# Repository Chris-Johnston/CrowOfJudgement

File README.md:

# Crow of Judgement

An LED Christmas ornament based on the "Crow of Judgement" meme.

# What?

# What, actually?

This is a meme which was common among my friends from school (aka "robocrob"). As a 
last-minute secret santa idea, I designed this circuitboard and made a few for gifts.

The circuit is really basic. It's just a switch, resistor, and two very bright red LEDs powered by a CR2032 coin cell battery.

I used KiCad to design the board. I traced the crow of judgement image
using Inkscape and the [svg2mod](https://github.com/svg2mod/svg2mod) tool to
convert my vector trace into the footprint.

I included pins on the board so that you can easily connect external power sources, if you want PWM or just don't want to use a battery.
The footprints for the parts are placed on the back, but the LEDs are meant
to go on the opposite side. This was done so that the silkscreen on the front
side was kept clean.

Because of the last minute nature of when I decided to start the project and
the amount of time it takes to have PCBs made (including in a pandemic),
I rushed the design of these by keeping them as simple as possible.
Maybe next year I could incorporate a microcontroller and make this more hackable. Only a few 4 AM nights were required to wrap this up.

# Build Guide

These are some basic instructions intended for those with some prior soldering experience
and some understanding of surface mount soldering, intended for those that I gifted
these ornaments to.

Also yes, I realize that many of these images are somewhat out of focus and
that my work surface was a bit dusty. No I don't plan on retaking these images.

## Parts

You should have:
  - The circuitboard
  - 2 LEDs (red)
  - 2 surface-mount resistors (40 ohm 1206 package, one extra)
  - 1 surface-mount switch
  - 1 coin-cell battery holder for a CR2032
  - 1 CR2032 battery
  - 1 piece of string to hang the ornament with

This page will provide some non-specific details for how to assemble the item.

## Tools Required

You'll need:
  - A soldering iron with a relatively fine tip
  - Solder
  - A room with good air circulation

Nice to have:
  - Diagonal cutters
  - Tweezers or pliers
  - Solder wick

# Assembly

## 1. Surface Mount Parts

The surface mount parts are the hardest part, luckily there aren't that many of them. It's good to get them out of the way first.
The challenge with these parts is that you have to keep them steady in the right place.

In general the technique I use is:
1. Tin one pad of the package very slightly.
2. Line up the package, ideally with tweezers or pliers.
3. With one hand heat the tinned pad and with the other hold the package in place.
4. Once the package is secure, solder the remaining pads. (In this case there are only 2.)

That's what I do here with the switch. I would actually recommend instead starting with the resistors, since I gave you 2, but the switch is
a bigger package so it will be easier.

Tin one pad for the component.

Place the part in place, hold it steady with the tweezers, heat up the pre-tinned side, then solder the other side.
The switch is not directional, so it can go either way. Neither are the resistors.

The switch should stand up a little bit. Unfortunately the part I picked kinda sucks. It sticks out from the board, and the switch is flush in the casing.
You will need a screwdriver or a pencil to flip the switch back and forth.

Next, I soldered the resistor. They are not directional, so don't worry if the numbers don't add up.
I provided 2 because they are very tiny and easy to lose.

If it turns out that the pads have too much solder, that's why solder wick is handy.

Congrats! That's the hard part!

## 2. Through-Hole Parts

Next up are the through-hole parts. If you know how to solder, you know how to solder these. If you don't for some reason, there are many guides or you can just DM me.

Both of these parts are directional. If you mess up everything completely in reverse, it will probably still work, but if any less then it won't work.

Start with the battery holder.

The square side of the battery holder goes on the **+** end, facing outwards on the **back** of the board. Place the board down on the battery holder and solder the two pins.

The battery holder pins are very sharp, and are in an area where you might place your hand! Be sure to trim the pins off when you are done so they aren't so sharp!

_This goes without saying, but you are also probably soldering with lead. Please don't lick the board, because lead isn't good for you._

All that's left are the LEDs.

You will probably know this already, but it's good to double check. LEDs have a flat edge on one side, one leg which is shorter, and you can also check what the inside of the LED looks like. **Match up the short leg (-) with the square hole (also labelled - on the back)!**

When soldering the LEDs, you may want to bend the pins a bit so that the LED stays in place. Even when pulled tight, it will have a small amount of wiggle room for adjustment. Be sure to trim these pins as well.

_Note:_ If the switch turns out to be really bad, you could probably use one leg of the LEDs to jump the two pins for the switch in its place. This will leave things permanently on.

## 3. Insert Battery + Hang with String

That's it! All that's left is to insert the battery. It should go in only one way, with the positive end of the battery facing outwards.

The holes in the top of the board can be used to thread twine through, with knots in the back to hold it in place.

# Some Things You Should Know

- The holes in the top are meant to run thread through to hang it up as an ornament. This is not pictured in the photos seen here, because I didn't have the thread yet.

- The power switch kinda sucks because I didn't get the right part. You'll want to use something to flip the switch.

- The LEDs are super bright, I have not done the math for how long it will stay on. I doubt it will be very long. Turn it off when you are done, or prepare some extra CR2032 batteries.

- The 3v3 and GND pins in the corner are meant to be an external power source. Want to hook this up to an Arduino? Go ahead!

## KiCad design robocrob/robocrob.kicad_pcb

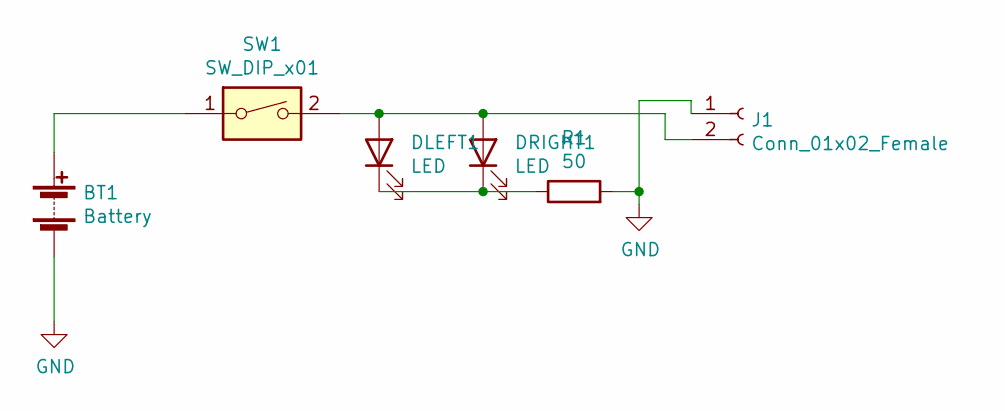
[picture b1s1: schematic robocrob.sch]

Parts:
BT1: Battery; BatteryHolder_ComfortableElectronic_CH273-2450_1x2450
DLEFT1: LED; LED_D5.0mm
DRIGHT1: LED; LED_D5.0mm
J1: Conn_01x02_Female; PinSocket_1x02_P2.54mm_Vertical
R1: 50; R_1206_3216Metric_Pad1.42x1.75mm_HandSolder
SW1: SW_DIP_x01; SW_DIP_SPSTx01_Slide_6.7x4.1mm_W8.61mm_P2.54mm_LowProfile

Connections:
GND: BT1.2 (-), J1.1, R1.2
unnamed: BT1.1 (+), SW1.1
unnamed: DLEFT1.1 (K), DRIGHT1.1 (K), R1.1
unnamed: DLEFT1.2 (A), DRIGHT1.2 (A), J1.2, SW1.2

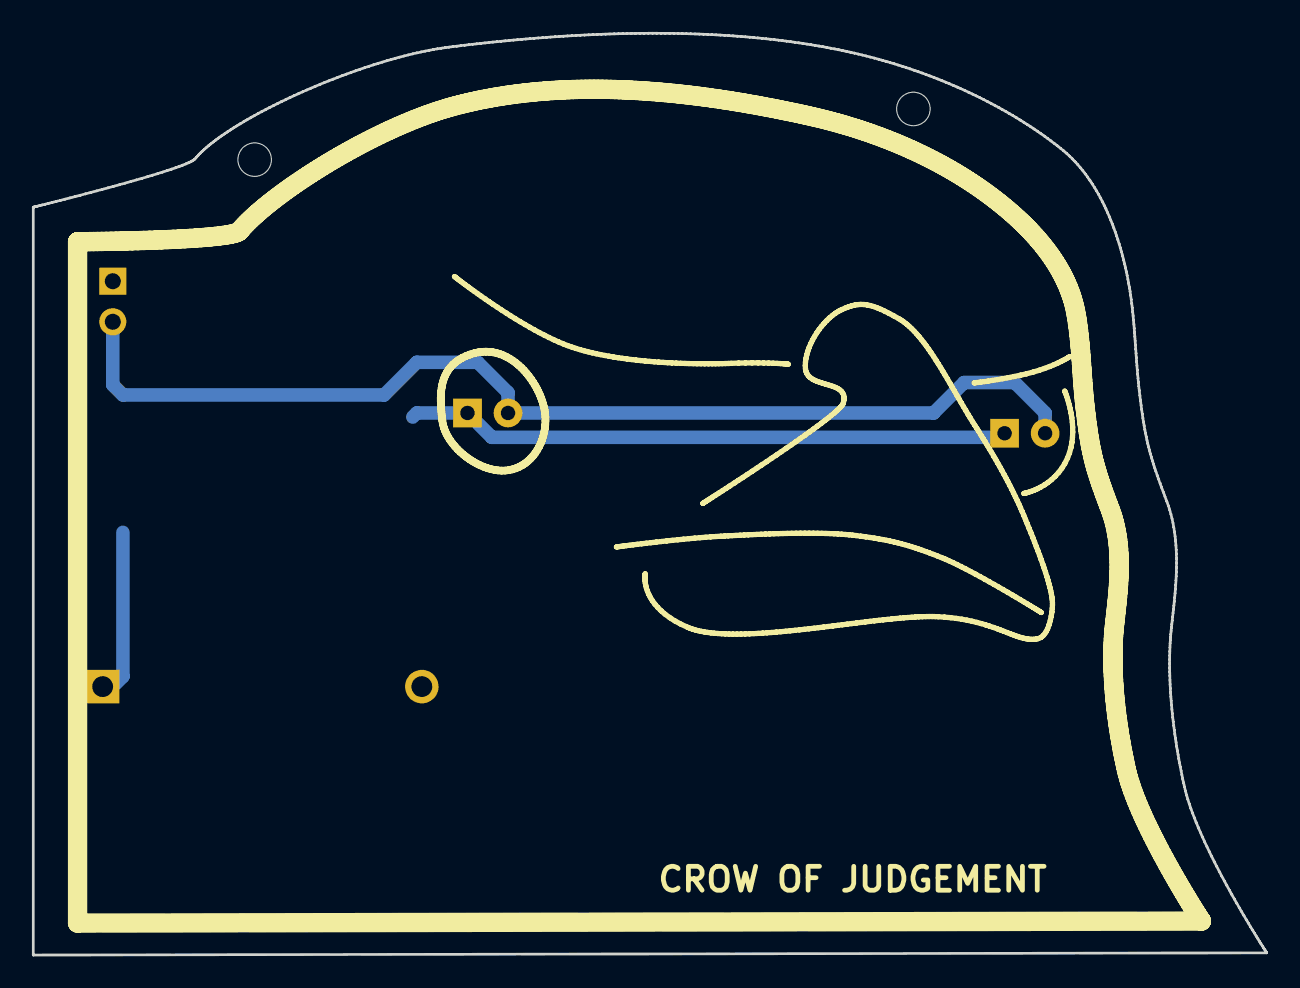
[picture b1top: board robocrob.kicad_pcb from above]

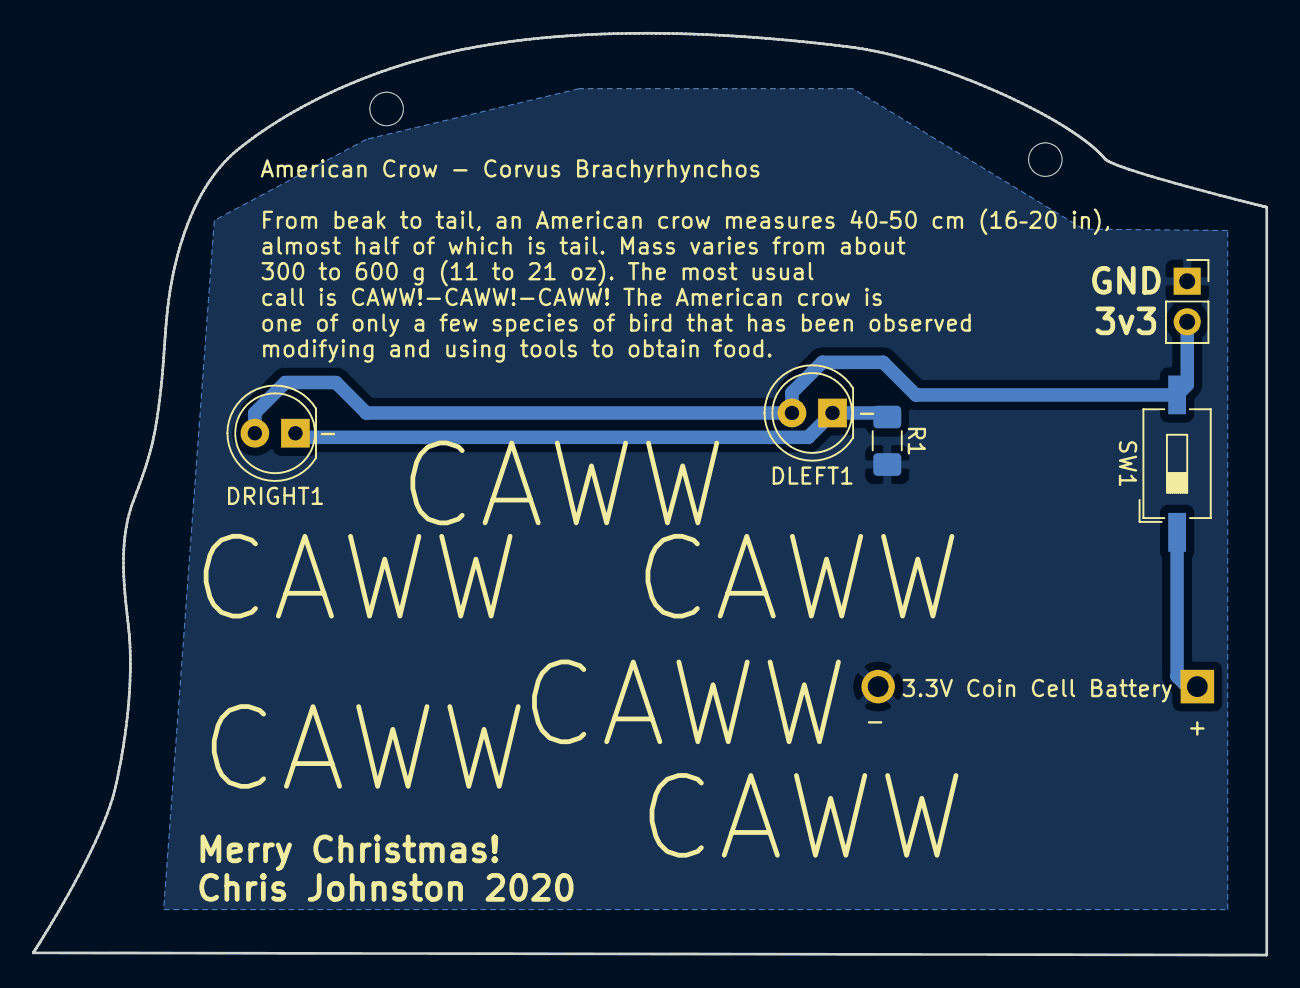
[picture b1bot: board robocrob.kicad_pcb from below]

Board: 2 copper layers, 77.3 x 57.8 mm, 7 parts (6 on the bottom side), 4 nets.

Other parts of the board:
svg2mod: G***; kicad_vectorcrob

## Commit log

2020-12-09 ship it or die trying
2020-12-09 gerberberberberberberbre
2020-12-24 Add project documentation
2020-12-24 remove gerber zipped files
2020-12-24 Create LICENSE
2020-12-24 Add thumbnail image
2020-12-24 Add gh pages index page
2020-12-24 modify gh pages content to use theme
2020-12-24 update gh pages content (maybe this would be better on the main repo and not here
2020-12-24 update front matter
2020-12-24 add gh link to the page
2020-12-24 what happens if I use the post layout
2020-12-24 Revert "what happens if I use the post layout" - it breaks stuff
    This reverts commit 07180fec74c905558dbcbff1e29dcd528175c275.
